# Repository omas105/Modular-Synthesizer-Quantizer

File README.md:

# Modular-Synthesizer-Quantizer
Modular Synthesizer Quantizer with Arduino nano and MCP4921 DAC

Inspired by [Hagiwo](https://note.com/solder_state/n/nde97a0516f03) and [luislutz's](https://github.com/luislutz/Arduino_Quantizer) design

<table>
  <tr>    
    <td></td>
    <td></td>
    <td></td>
  </tr>
 </table>

## Inputs
Pitch CV [0-7V] - Voltage to be quantized.

Trigger [2-12V] - Generate new quantized CV.

Transpose [0-5V] - Transpose quantized CV.

## Outputs
QV [0-9V] - Quantized CV.

Gate [0-10V] - Generates a pulse when QV i changed.

## Knops and switches
Transpose knop - Transpose QV 7 octaves.

Trigger switch - In OFF state QV is only changes when reciving a input trigger signal. In ON state QV is changes when pitch CV or transpose changes to a new note.

Offset switch - Transpose QV 2 octaves.

Mode selector - Encoder to change scales, transpose mode and root note.

<table>
  <tr>
   <td><b>Scale</b></td>
   <td><b>Root note</b></td>
   <td><b>Transpose mode</b></td>   
 </tr>
  <td>Turn mode knop</td>
  <td>Click and hold mode knop while turning</td>
  <td>Double click and turn mode knop</td>
 <tr>    
   <td>
    
| Number | Scale |
|--------|-------|
|0 |Major|
|1 |Major pentatonic|
|2 |Major pentatonic + 7|
|3 |Natural Minor|
|4 |Minor pentatonic|
|5 |Harmonic minor|
|6 |Melodic minor|
|7 |Blues|
|8 |Chromatic|
|9 |Octave|
   </td>

   <td>
    
| Display | Note |
|---------|------|
| C | C |
| C. | C# |
| d | D |
| d. | D# |
| E | E |
| F | F |
| F. | F# |
| G | G |
| G. | G# |
| A | A |
| A. | A# |
| b | B |
   </td>

   <td>
     
| Display | Mode |
|-|-|
| Top | 12 Semitones
| Midt | 7 Semitones|
| Bottom | 1 Semitone|   
   </td>
  
  </tr>
 </table>

# PCB

<table>
  <tr>
    <td>Front</td>
    <td>Back</td>
  </tr>
  <tr>    
    <td></td>
    <td></td>
  </tr>
 </table>

## License

[GNU General Public License (GPLv3)](LICENSE)

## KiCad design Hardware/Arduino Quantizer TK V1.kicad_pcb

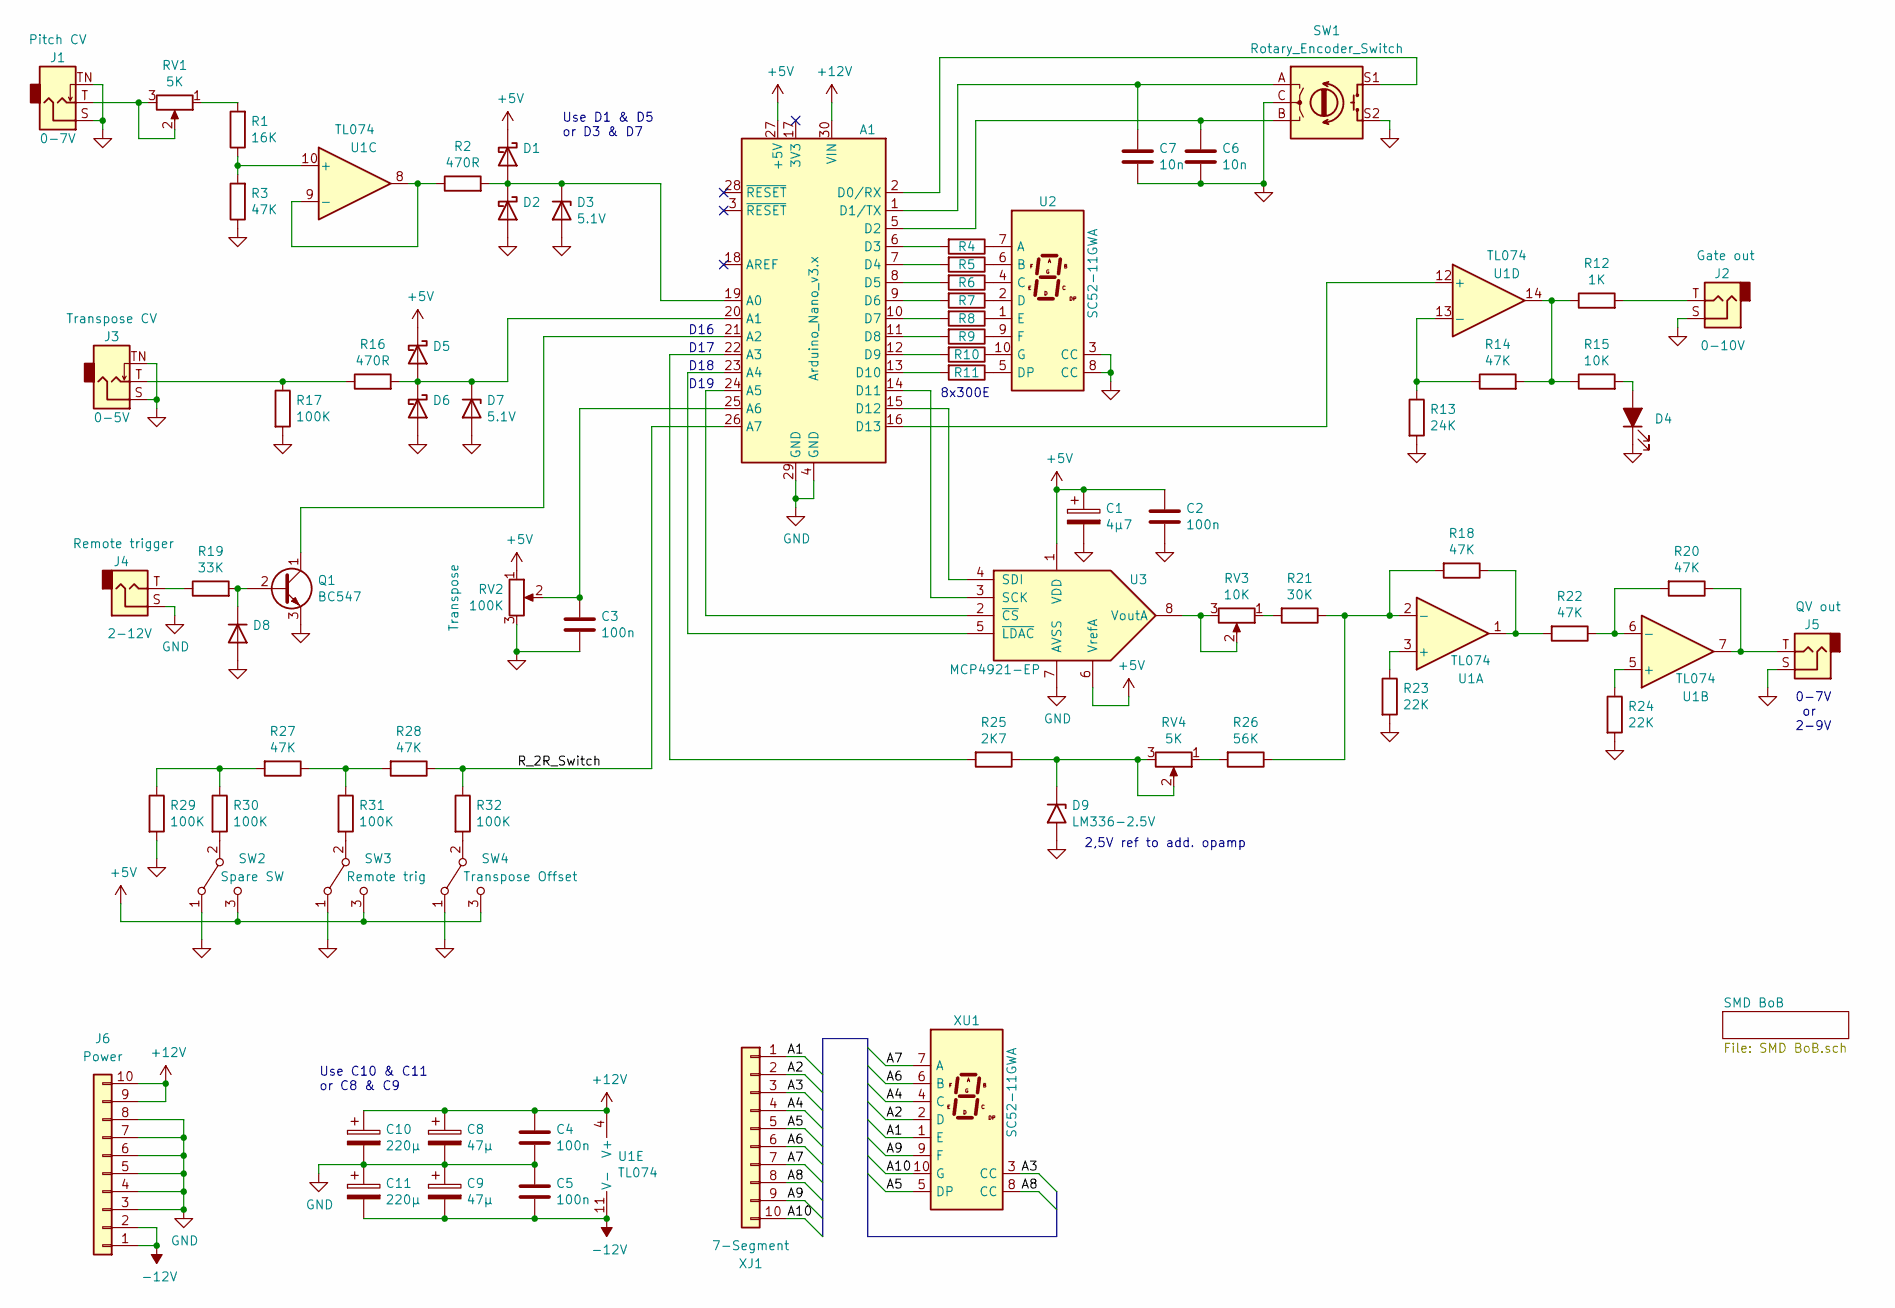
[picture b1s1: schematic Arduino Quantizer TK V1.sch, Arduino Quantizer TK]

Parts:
A1: Arduino_Nano_v3.x; Arduino_Nano
C1: 4µ7; CP_Radial_D5.0mm_P2.00mm_P5.00mm
C2, C3, C4, C5: 100n; C_Rect_L7.0mm_W2.0mm_P2.50_P5.00mm
C6, C7: 10n; C_Rect_L7.0mm_W2.0mm_P2.50_P5.00mm
C8, C9: 47µ; CP_Radial_D6.3mm_P2.50mm
C10, C11: 220µ; CP_Radial_D10.0mm_P5.00mm
D1, D2, D5, D6: BAT43; D_DO-35_SOD27_P7.62mm_Horizontal
D3, D7: 1N4733 5.1V; D_DO-41_SOD81_P10.16mm_Horizontal
D4: Gate out LED; PinHeader_1x02_P2.54mm_Vertical
D8: 1N4148; D_DO-35_SOD27_P7.62mm_Horizontal
D9: LM336-2.5V; TO-92_Inline_Wide_Longpads
J1: Pitch CV; Jack_PinHeader_1x02_P2.54mm_Vertical
J2: Gate out; Jack_PinHeader_1x02_P2.54mm_Vertical
J3: Transpose CV; Jack_PinHeader_1x02_P2.54mm_Vertical
J4: Remote trigger; Jack_PinHeader_1x02_P2.54mm_Vertical
J5: QV out; Jack_6.35mm_Neutrik_NMJ6HFD2_Horizontal
J6: Power; IDC-Header_2x05_P2.54mm_Vertical
Q1: BC547; TO-92_Inline_Wide_Longpads
R1: 16K; R_Axial_DIN0207_L6.3mm_D2.5mm_P10.16mm_Horizontal
R2, R16: 470R; R_Axial_DIN0207_L6.3mm_D2.5mm_P10.16mm_Horizontal
R3, R14, R18, R20, R22, R27, R28: 47K; R_Axial_DIN0207_L6.3mm_D2.5mm_P10.16mm_Horizontal
R4, R5, R6, R7, R8, R9, R10, R11: 300E; R_Axial_DIN0207_L6.3mm_D2.5mm_P10.16mm_Horizontal
R12: 1K; R_Axial_DIN0207_L6.3mm_D2.5mm_P10.16mm_Horizontal
R13: 24K; R_Axial_DIN0207_L6.3mm_D2.5mm_P10.16mm_Horizontal
R15: 10K; R_Axial_DIN0207_L6.3mm_D2.5mm_P10.16mm_Horizontal
R17, R29, R30, R31, R32: 100K; R_Axial_DIN0207_L6.3mm_D2.5mm_P10.16mm_Horizontal
R19: 33K; R_Axial_DIN0207_L6.3mm_D2.5mm_P10.16mm_Horizontal
R21: 30K; R_Axial_DIN0207_L6.3mm_D2.5mm_P10.16mm_Horizontal
R23, R24: 22K; R_Axial_DIN0207_L6.3mm_D2.5mm_P10.16mm_Horizontal
R25: 2K7; R_Axial_DIN0207_L6.3mm_D2.5mm_P10.16mm_Horizontal
R26: 56K; R_Axial_DIN0207_L6.3mm_D2.5mm_P10.16mm_Horizontal
RV1, RV4: 5K; Potentiometer_Bourns_3296W_Vertical_longpads_2
RV2: 100K; PinHeader_1x03_P2.54mm_Vertical
RV3: 10K; Potentiometer_Bourns_3296W_Vertical_longpads_2
SW1: Rotary_Encoder_Switch; Encoder_with_Switch_PinHeader_2x03_P2.54mm_Vertical
SW2: Spare SW; PinHeader_1x03_P2.54mm_Vertical
SW3: Remote trig; PinHeader_1x03_P2.54mm_Vertical
SW4: Transpose Offset; PinHeader_1x03_P2.54mm_Vertical
U1: TL074; DIP-14_W7.62mm_Socket_LongPads
U2: SC52-11GWA; Eurorack_power_IDC-Header_2x05_P2.54mm_Vertical
U3: MCP4921-EP; DIP-8_W7.62mm_Socket_LongPads
XJ1: 7-Segment; IDC-Header_2x05_P2.54mm_Vertical
XU1: SC52-11GWA; 7Segment_SC52-11GWA

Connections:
+5V: A1.27 (+5V), C1.1, C2.1, D1.1 (K), D5.1 (K), RV2.1, SW2.3 (C), SW3.3 (C), SW4.3 (C), U3.1 (VDD), U3.6 (VrefA)
+12V: A1.30 (VIN), C4.1, C8.1, C10.1, J6.9, J6.10, U1.4 (V+)
-12V: C5.2, C9.2, C11.2, J6.1, J6.2, U1.11 (V-)
/A1: XJ1.1, XU1.1 (E)
/A2: XJ1.2, XU1.2 (D)
/A3: XJ1.3, XU1.3 (CC)
/A4: XJ1.4, XU1.4 (C)
/A5: XJ1.5, XU1.5 (DP)
/A6: XJ1.6, XU1.6 (B)
/A7: XJ1.7, XU1.7 (A)
/A8: XJ1.8, XU1.8 (CC)
/A9: XJ1.9, XU1.9 (F)
/A10: XJ1.10, XU1.10 (G)
/R_2R_Switch: A1.26 (A7), R28.1, R32.1
GND: A1.4 (GND), A1.29 (GND), C1.2, C2.2, C3.2, C4.2, C5.1, C6.2, C7.2, C8.2, C9.1, C10.2, C11.1, D2.2 (A), D3.2 (A), D4.1 (K), D6.2 (A), D7.2 (A), D8.2 (A), D9.3 (A), J1.S, J1.TN, J2.S, J3.S, J3.TN, J4.S, J5.S, J6.3, J6.4, J6.5, J6.6, J6.7, J6.8, Q1.3 (E), R3.1, R13.2, R17.2, R23.2, R24.2, R29.2, RV2.3, SW1.C, SW1.S2, SW2.1 (A), SW3.1 (A), SW4.1 (A), U2.3 (CC), U2.8 (CC), U3.7 (AVSS)
unnamed: A1.1 (D1/TX), C7.1, SW1.A
unnamed: A1.2 (D0/RX), SW1.S1
unnamed: A1.5 (D2), C6.1, SW1.B
unnamed: A1.6 (D3), R4.2
unnamed: A1.7 (D4), R5.2
unnamed: A1.8 (D5), R6.2
unnamed: A1.9 (D6), R7.2
unnamed: A1.10 (D7), R8.2
unnamed: A1.11 (D8), R9.2
unnamed: A1.12 (D9), R10.2
unnamed: A1.13 (D10), R11.2
unnamed: A1.14 (D11), U3.3 (SCK)
unnamed: A1.15 (D12), U3.4 (SDI)
unnamed: A1.16 (D13), U1.12 (+)
unnamed: A1.19 (A0), D1.2 (A), D2.1 (K), D3.1 (K), R2.2
unnamed: A1.20 (A1), D5.2 (A), D6.1 (K), D7.1 (K), R16.2
unnamed: A1.21 (A2), Q1.1 (C)
unnamed: A1.22 (A3), R25.2
unnamed: A1.23 (A4), U3.5 (~LDAC~)
unnamed: A1.24 (A5), U3.2 (~CS~)
unnamed: A1.25 (A6), C3.1, RV2.2
unnamed: D4.2 (A), R15.2
unnamed: D8.1 (K), Q1.2 (B), R19.2
unnamed: D9.2 (K), R25.1, RV4.2, RV4.3
unnamed: J1.T, RV1.2, RV1.3
unnamed: J2.T, R12.2
unnamed: J3.T, R16.1, R17.1
unnamed: J4.T, R19.1
unnamed: J5.T, R20.1, U1.7
unnamed: R1.1, R3.2, U1.10 (+)
unnamed: R1.2, RV1.1
unnamed: R2.1, U1.8, U1.9 (-)
unnamed: R4.1, U2.7 (A)
unnamed: R5.1, U2.6 (B)
unnamed: R6.1, U2.4 (C)
unnamed: R7.1, U2.2 (D)
unnamed: R8.1, U2.1 (E)
unnamed: R9.1, U2.9 (F)
unnamed: R10.1, U2.10 (G)
unnamed: R11.1, U2.5 (DP)
unnamed: R12.1, R14.2, R15.1, U1.14
unnamed: R13.1, R14.1, U1.13 (-)
unnamed: R18.1, R22.2, U1.1
unnamed: R18.2, R21.1, R26.1, U1.2 (-)
unnamed: R20.2, R22.1, U1.6 (-)
unnamed: R21.2, RV3.1
unnamed: R23.1, U1.3 (+)
unnamed: R24.1, U1.5 (+)
unnamed: R26.2, RV4.1
unnamed: R27.1, R28.2, R31.1
unnamed: R27.2, R29.1, R30.1
unnamed: R30.2, SW2.2 (B)
unnamed: R31.2, SW3.2 (B)
unnamed: R32.2, SW4.2 (B)
unnamed: RV3.2, RV3.3, U3.8 (VoutA)

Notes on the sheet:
0-7V or 2-9V
2,5V ref to add. opamp
8x300E
D16
D17
D18
D19
Use C10 & C11 or C8 & C9
Use D1 & D5 or D3 & D7

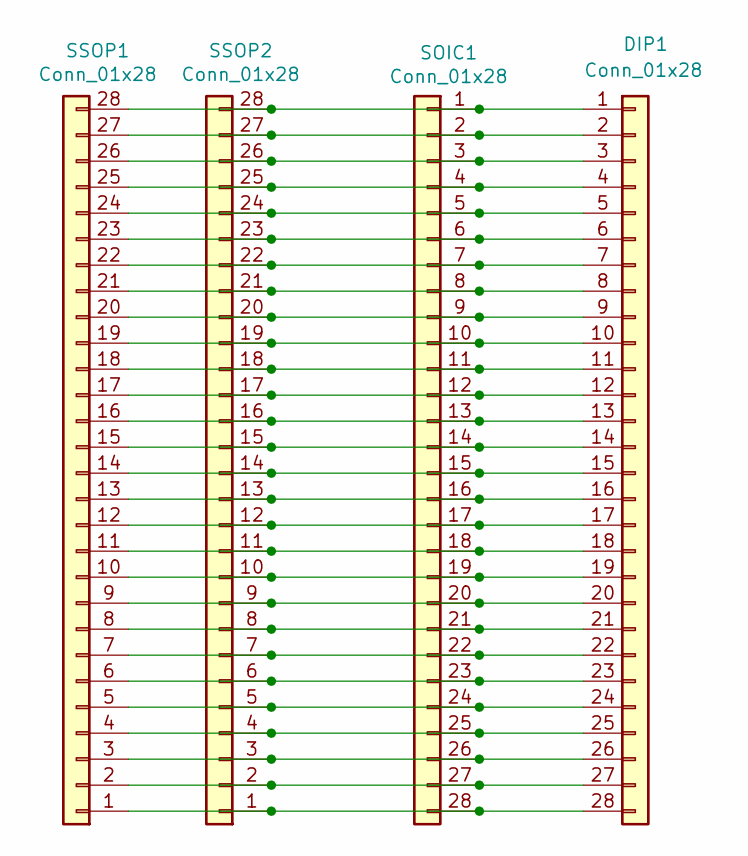
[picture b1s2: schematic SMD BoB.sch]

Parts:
DIP1: Conn_01x28; DIP-28_W15.24mm_Socket
SOIC1: Conn_01x28; SOIC-28W_7.5x18.7mm_P1.27mm
SSOP1: Conn_01x28; TSSOP-28_6.1x9.7mm_P0.65mm
SSOP2: Conn_01x28; TSSOP-28_4.4x9.7mm_P0.65mm

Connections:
unnamed: DIP1.1, SOIC1.1, SSOP1.28, SSOP2.28
unnamed: DIP1.2, SOIC1.2, SSOP1.27, SSOP2.27
unnamed: DIP1.3, SOIC1.3, SSOP1.26, SSOP2.26
unnamed: DIP1.4, SOIC1.4, SSOP1.25, SSOP2.25
unnamed: DIP1.5, SOIC1.5, SSOP1.24, SSOP2.24
unnamed: DIP1.6, SOIC1.6, SSOP1.23, SSOP2.23
unnamed: DIP1.7, SOIC1.7, SSOP1.22, SSOP2.22
unnamed: DIP1.8, SOIC1.8, SSOP1.21, SSOP2.21
unnamed: DIP1.9, SOIC1.9, SSOP1.20, SSOP2.20
unnamed: DIP1.10, SOIC1.10, SSOP1.19, SSOP2.19
unnamed: DIP1.11, SOIC1.11, SSOP1.18, SSOP2.18
unnamed: DIP1.12, SOIC1.12, SSOP1.17, SSOP2.17
unnamed: DIP1.13, SOIC1.13, SSOP1.16, SSOP2.16
unnamed: DIP1.14, SOIC1.14, SSOP1.15, SSOP2.15
unnamed: DIP1.15, SOIC1.15, SSOP1.14, SSOP2.14
unnamed: DIP1.16, SOIC1.16, SSOP1.13, SSOP2.13
unnamed: DIP1.17, SOIC1.17, SSOP1.12, SSOP2.12
unnamed: DIP1.18, SOIC1.18, SSOP1.11, SSOP2.11
unnamed: DIP1.19, SOIC1.19, SSOP1.10, SSOP2.10
unnamed: DIP1.20, SOIC1.20, SSOP1.9, SSOP2.9
unnamed: DIP1.21, SOIC1.21, SSOP1.8, SSOP2.8
unnamed: DIP1.22, SOIC1.22, SSOP1.7, SSOP2.7
unnamed: DIP1.23, SOIC1.23, SSOP1.6, SSOP2.6
unnamed: DIP1.24, SOIC1.24, SSOP1.5, SSOP2.5
unnamed: DIP1.25, SOIC1.25, SSOP1.4, SSOP2.4
unnamed: DIP1.26, SOIC1.26, SSOP1.3, SSOP2.3
unnamed: DIP1.27, SOIC1.27, SSOP1.2, SSOP2.2
unnamed: DIP1.28, SOIC1.28, SSOP1.1, SSOP2.1

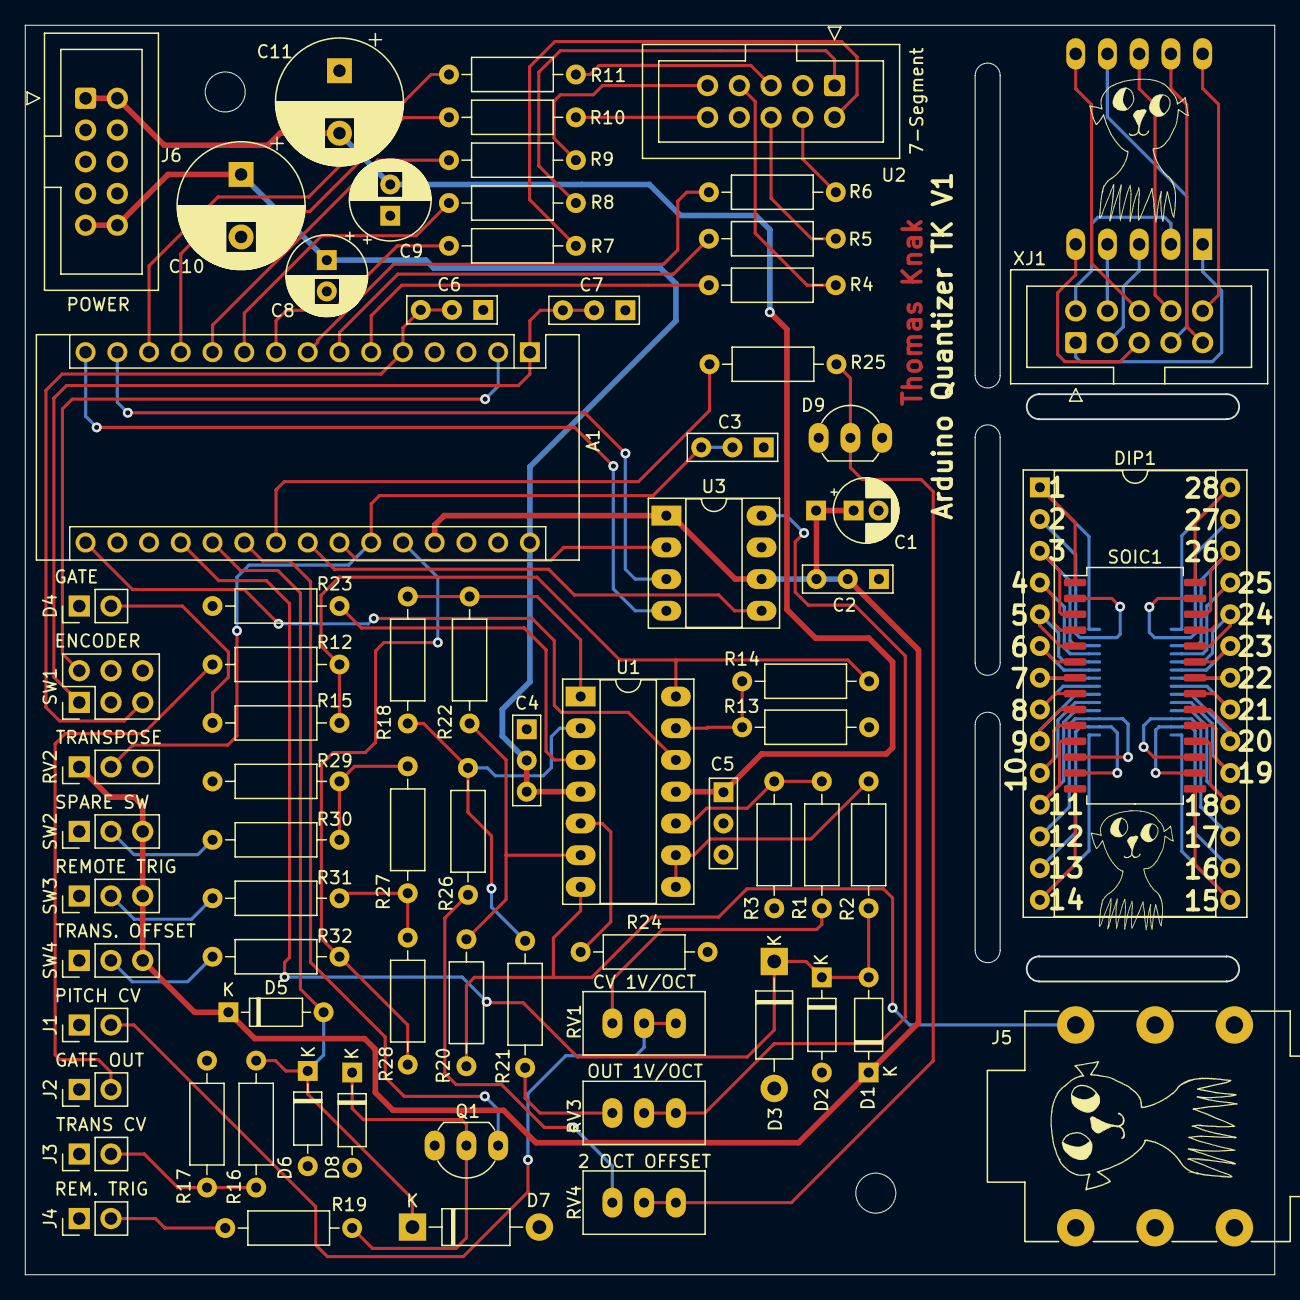
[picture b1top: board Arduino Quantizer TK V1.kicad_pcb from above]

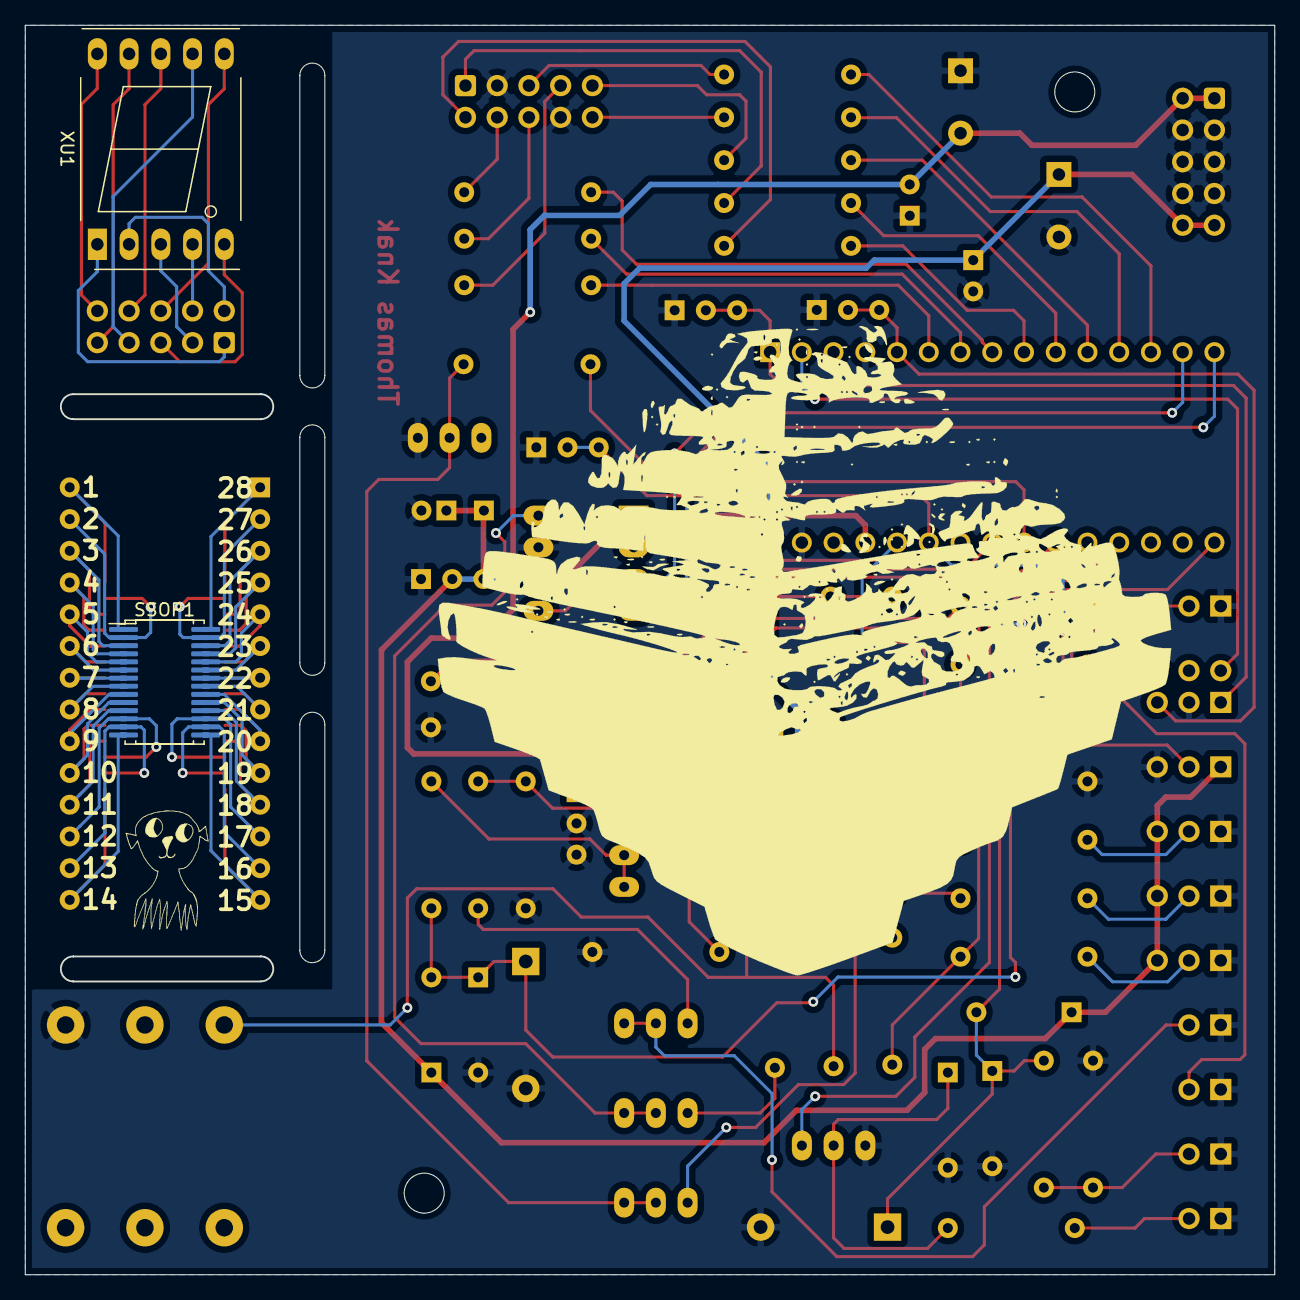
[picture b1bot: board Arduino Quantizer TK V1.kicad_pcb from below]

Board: 2 copper layers, 100.0 x 100.0 mm, 77 parts (3 on the bottom side), 98 nets.

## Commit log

2022-11-03 init
2022-11-03 init push
2022-11-03 modul image
2023-06-30 added LICENSE
2023-06-30 License added
